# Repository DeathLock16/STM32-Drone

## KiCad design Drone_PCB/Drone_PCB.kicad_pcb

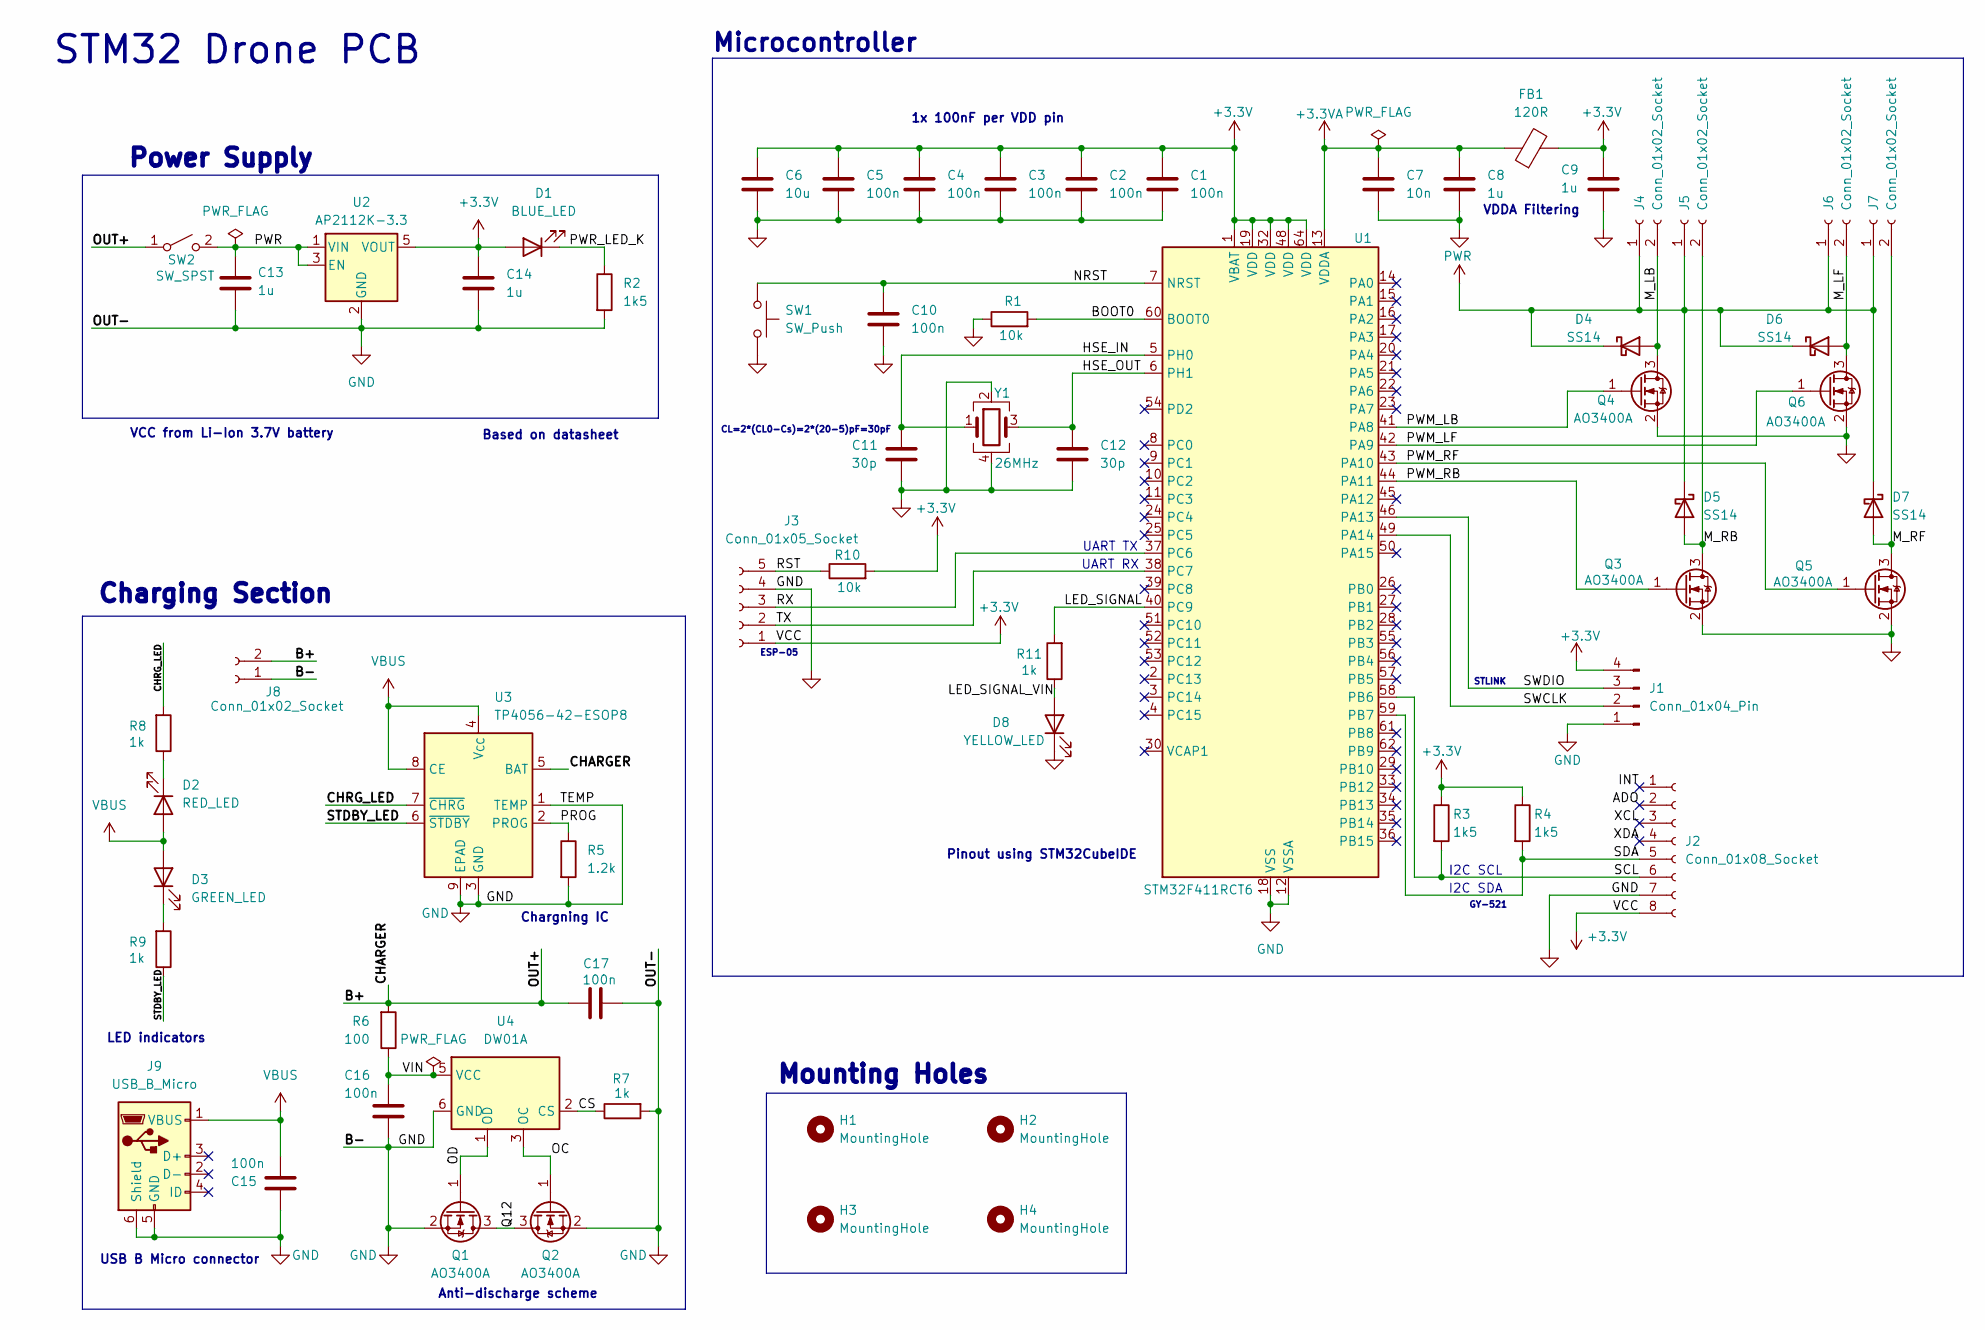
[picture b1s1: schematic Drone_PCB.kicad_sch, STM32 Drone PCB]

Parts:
C1, C2, C3, C4, C5, C10, C15, C16, C17: 100n; C_0402_1005Metric
C6: 10u; C_0603_1608Metric
C7: 10n; C_0402_1005Metric
C8, C9, C13, C14: 1u; C_0402_1005Metric
C11, C12: 30p; C_0402_1005Metric
D1: BLUE_LED; LED_0603_1608Metric
D2: RED_LED; LED_0603_1608Metric
D3: GREEN_LED; LED_0603_1608Metric
D4, D5, D6, D7: SS14; D_SMA
D8: YELLOW_LED; LED_0603_1608Metric
FB1: 120R; L_0603_1608Metric
H1, H2, H3, H4: MountingHole; MountingHole_2.2mm_M2
J1: Conn_01x04_Pin; PinHeader_1x04_P2.54mm_Vertical
J2: Conn_01x08_Socket; PinSocket_1x08_P2.54mm_Vertical
J3: Conn_01x05_Socket; PinSocket_1x05_P2.54mm_Vertical
J4, J5, J6, J7, J8: Conn_01x02_Socket; PinSocket_1x02_P2.54mm_Vertical
J9: USB_B_Micro; USB_Micro-B_Wuerth_629105150521
Q1, Q2, Q3, Q4, Q5, Q6: AO3400A; SOT-23
R1, R10: 10k; R_0402_1005Metric
R2, R3, R4: 1k5; R_0402_1005Metric
R5: 1.2k; R_0402_1005Metric
R6: 100; R_0402_1005Metric
R7, R8, R9, R11: 1k; R_0402_1005Metric
SW1: SW_Push; SW_PUSH_6mm
SW2: SW_SPST; SW_CK_JS202011AQN_DPDT_Angled
U1: STM32F411RCT6; LQFP-64_10x10mm_P0.5mm
U2: AP2112K-3.3; SOT-23-5
U3: TP4056-42-ESOP8; SOIC-8-1EP_3.9x4.9mm_P1.27mm_EP2.41x3.3mm_ThermalVias
U4: DW01A; SOT-23-6
Y1: 26MHz; Crystal_SMD_3225-4Pin_3.2x2.5mm

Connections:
+3.3V: C1.1, C2.1, C3.1, C4.1, C5.1, C6.1, C9.1, C14.1, D1.2 (A), FB1.2, J1.4, J2.8, J3.1, R3.1, R4.1, R10.2, U1.1 (VBAT), U1.19 (VDD), U1.32 (VDD), U1.48 (VDD), U1.64 (VDD), U2.5 (VOUT)
+3.3VA: C7.1, C8.1, FB1.1, U1.13 (VDDA)
/ADO: J2.2
/B+: C17.1, J8.2, R6.2, SW2.1 (A), U3.5 (BAT)
/BOOT0: R1.2, U1.60 (BOOT0)
/CHRG_LED: R8.2, U3.7 (~CHRG)
/CS: R7.1, U4.2 (CS)
/HSE_IN: C11.1, U1.5 (PH0), Y1.1
/HSE_OUT: C12.1, U1.6 (PH1), Y1.3
/INT: J2.1
/LED_SIGNAL: R11.2, U1.40 (PC9)
/LED_SIGNAL_VIN: D8.2 (A), R11.1
/M_LB: D4.2 (A), J4.2, Q4.3 (D)
/M_LF: D6.2 (A), J6.2, Q6.3 (D)
/M_RB: D5.2 (A), J5.2, Q3.3 (D)
/M_RF: D7.2 (A), J7.2, Q5.3 (D)
/NRST: C10.1, SW1.1, U1.7 (NRST)
/OC: Q2.1 (G), U4.3 (OC)
/OD: Q1.1 (G), U4.1 (OD)
/PROG: R5.1, U3.2 (PROG)
/PWM_LB: Q4.1 (G), U1.41 (PA8)
/PWM_LF: Q6.1 (G), U1.42 (PA9)
/PWM_RB: Q3.1 (G), U1.44 (PA11)
/PWM_RF: Q5.1 (G), U1.43 (PA10)
/PWR_LED_K: D1.1 (K), R2.1
/Q12: Q1.3 (D), Q2.3 (D)
/RST: J3.5, R10.1
/RX: J3.3, U1.37 (PC6)
/SCL: J2.6, R3.2, U1.58 (PB6)
/SDA: J2.5, R4.2, U1.59 (PB7)
/STDBY_LED: R9.1, U3.6 (~STDBY)
/SWCLK: J1.2, U1.49 (PA14)
/SWDIO: J1.3, U1.46 (PA13)
/TX: J3.2, U1.38 (PC7)
/VIN: C16.1, R6.1, U4.5 (VCC)
/XCL: J2.3
/XDA: J2.4
GND: C1.2, C2.2, C3.2, C4.2, C5.2, C6.2, C7.2, C8.2, C9.2, C10.2, C11.2, C12.2, C13.2, C14.2, C15.1, C16.2, C17.2, D8.1 (K), J1.1, J2.7, J3.4, J8.1, J9.5 (GND), J9.6 (Shield), Q1.2 (S), Q2.2 (S), Q3.2 (S), Q4.2 (S), Q5.2 (S), Q6.2 (S), R1.1, R2.2, R5.2, R7.2, SW1.2, U1.12 (VSSA), U1.18 (VSS), U1.31 (VSS), U1.47 (VSS), U1.63 (VSS), U2.2 (GND), U3.1 (TEMP), U3.3 (GND), U3.9 (EPAD), U4.6 (GND), Y1.2, Y1.4
unnamed: D2.1 (K), R8.1
unnamed: D3.1 (K), R9.2
PWR: C13.1, D4.1 (K), D5.1 (K), D6.1 (K), D7.1 (K), J4.1, J5.1, J6.1, J7.1, SW2.2 (B), U2.1 (VIN), U2.3 (EN)
VBUS: C15.2, D2.2 (A), D3.2 (A), J9.1 (VBUS), U3.4 (V_{CC}), U3.8 (CE)

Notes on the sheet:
CL=2*(CL0-Cs)=2*(20-5)pF=30pF
Mounting Holes
GY-521
Pinout using STM32CubeIDE
UART TX
USB B Micro connector
UART RX
Power Supply
LED indicators
Chargning IC
VCC from Li-Ion 3.7V battery
I2C SDA
STM32 Drone PCB
1x 100nF per VDD pin
Based on datasheet
ESP-05
Anti-discharge scheme
Microcontroller
Charging Section
VDDA Filtering
STLINK
I2C SCL

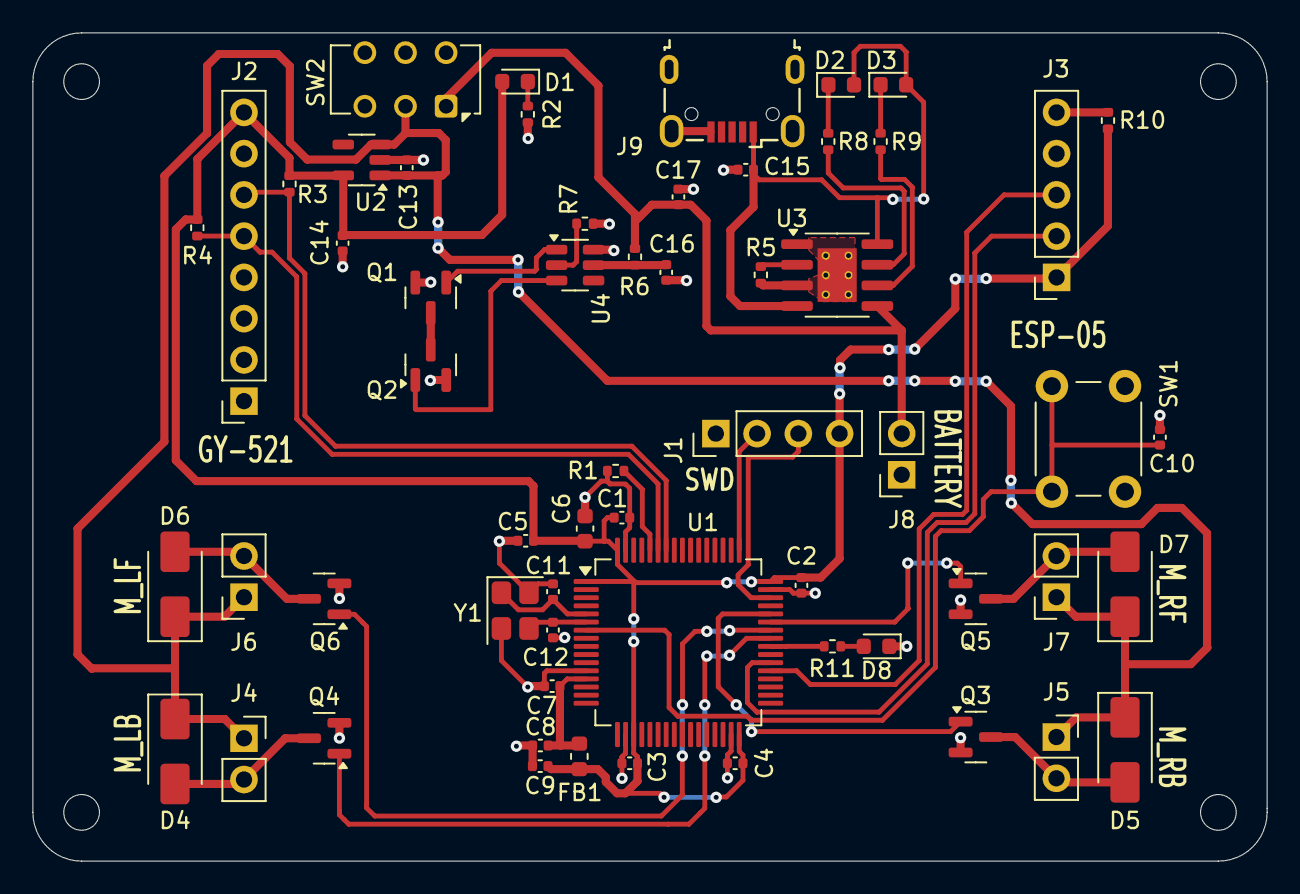
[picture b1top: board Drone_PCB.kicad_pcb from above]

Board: 2 copper layers, 76.0 x 51.0 mm, 63 parts (0 on the bottom side), 38 nets.

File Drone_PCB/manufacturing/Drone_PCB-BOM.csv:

"Reference","Qty","Value","DNP","Exclude from BOM","Exclude from Board","Footprint","Datasheet"
"C1,C2,C3,C4,C5,C10,C15,C16,C17","9","100n","","","","Capacitor_SMD:C_0402_1005Metric","~"
"C6","1","10u","","","","Capacitor_SMD:C_0603_1608Metric","~"
"C7","1","10n","","","","Capacitor_SMD:C_0402_1005Metric","~"
"C8,C9,C13,C14","4","1u","","","","Capacitor_SMD:C_0402_1005Metric","~"
"C11,C12","2","30p","","","","Capacitor_SMD:C_0402_1005Metric","~"
"D1","1","BLUE_LED","","","","LED_SMD:LED_0603_1608Metric","~"
"D2","1","RED_LED","","","","LED_SMD:LED_0603_1608Metric","~"
"D3","1","GREEN_LED","","","","LED_SMD:LED_0603_1608Metric","~"
"D4,D5,D6,D7","4","SS14","","","","Diode_SMD:D_SMA","https://www.vishay.com/docs/88746/ss12.pdf"
"D8","1","YELLOW_LED","","","","LED_SMD:LED_0603_1608Metric","~"
"FB1","1","120R","","","","Inductor_SMD:L_0603_1608Metric","~"
"J1","1","Conn_01x04_Pin","","","","Connector_PinHeader_2.54mm:PinHeader_1x04_P2.54mm_Vertical","~"
"J2","1","Conn_01x08_Socket","","","","Connector_PinSocket_2.54mm:PinSocket_1x08_P2.54mm_Vertical","~"
"J3","1","Conn_01x05_Socket","","","","Connector_PinSocket_2.54mm:PinSocket_1x05_P2.54mm_Vertical","~"
"J4,J5,J6,J7,J8","5","Conn_01x02_Socket","","","","Connector_PinSocket_2.54mm:PinSocket_1x02_P2.54mm_Vertical","~"
"J9","1","USB_B_Micro","","","","Connector_USB:USB_Micro-B_Wuerth_629105150521","~"
"Q1,Q2,Q3,Q4,Q5,Q6","6","AO3400A","","","","Package_TO_SOT_SMD:SOT-23","http://www.aosmd.com/pdfs/datasheet/AO3400A.pdf"
"R1,R10","2","10k","","","","Resistor_SMD:R_0402_1005Metric","~"
"R2,R3,R4","3","1k5","","","","Resistor_SMD:R_0402_1005Metric","~"
"R5","1","1.2k","","","","Resistor_SMD:R_0402_1005Metric","~"
"R6","1","100","","","","Resistor_SMD:R_0402_1005Metric","~"
"R7,R8,R9,R11","4","1k","","","","Resistor_SMD:R_0402_1005Metric","~"
"SW1","1","SW_Push","","","","Button_Switch_THT:SW_PUSH_6mm","~"
"SW2","1","SW_SPST","","","","Button_Switch_THT:SW_CK_JS202011AQN_DPDT_Angled","~"
"U1","1","STM32F411RCT6","","","","Package_QFP:LQFP-64_10x10mm_P0.5mm","https://www.st.com/resource/en/datasheet/stm32f411rc.pdf"
"U2","1","AP2112K-3.3","","","","Package_TO_SOT_SMD:SOT-23-5","https://www.diodes.com/assets/Datasheets/AP2112.pdf"
"U3","1","TP4056-42-ESOP8","","","","Package_SO:SOIC-8-1EP_3.9x4.9mm_P1.27mm_EP2.41x3.3mm_ThermalVias","https://www.lcsc.com/datasheet/lcsc_datasheet_2410121619_TOP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"
"U4","1","DW01A","","","","Package_TO_SOT_SMD:SOT-23-6","https://hmsemi.com/downfile/DW01A.PDF"
"Y1","1","26MHz","","","","Crystal:Crystal_SMD_3225-4Pin_3.2x2.5mm","~"

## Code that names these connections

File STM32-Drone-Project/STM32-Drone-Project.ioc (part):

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Mcu.Name=STM32F411R(C-E)Tx
Mcu.Package=LQFP64
Mcu.UserName=STM32F411RCTx
PA10.GPIOParameters=GPIO_Label
PA10.GPIO_Label=MOTOR_RF
PA10.Signal=S_TIM1_CH3
PA11.GPIOParameters=GPIO_Label
PA11.GPIO_Label=MOTOR_RB
PA11.Signal=S_TIM1_CH4
PA13.Mode=Serial_Wire
PA13.Signal=SYS_JTMS-SWDIO
PA14.Mode=Serial_Wire
PA14.Signal=SYS_JTCK-SWCLK
PA8.GPIOParameters=GPIO_Label
PA8.GPIO_Label=MOTOR_LB
PA8.Signal=S_TIM1_CH1
PA9.GPIOParameters=GPIO_Label
PA9.GPIO_Label=MOTOR_LF
PA9.Signal=S_TIM1_CH2
PB6.Mode=I2C
PB6.Signal=I2C1_SCL
PB7.Mode=I2C
PB7.Signal=I2C1_SDA
PC14-OSC32_IN.Mode=LSE-External-Oscillator
PC14-OSC32_IN.Signal=RCC_OSC32_IN
PC15-OSC32_OUT.Mode=LSE-External-Oscillator
PC15-OSC32_OUT.Signal=RCC_OSC32_OUT
PC6.Mode=Asynchronous
PC6.Signal=USART6_TX
PC7.Mode=Asynchronous
PC7.Signal=USART6_RX
PC9.GPIOParameters=GPIO_Label
PC9.GPIO_Label=LED_SIGNAL
PC9.Signal=GPIO_Output
PH0\ -\ OSC_IN.Mode=HSE-External-Oscillator
PH0\ -\ OSC_IN.Signal=RCC_OSC_IN
PH1\ -\ OSC_OUT.Mode=HSE-External-Oscillator
PH1\ -\ OSC_OUT.Signal=RCC_OSC_OUT
RCC.HSE_VALUE=26000000
RCC.SYSCLKFreq_VALUE=26000000
RCC.SYSCLKSource=RCC_SYSCLKSOURCE_HSE
board=custom

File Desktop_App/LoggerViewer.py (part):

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
        self.ax_pwm.set_title("PWM")
        self.ax_pwm.set_ylabel("pwm")
        self.ax_pwm.plot(t, df["pwm_lf"].values, label="pwm_lf")
        self.ax_pwm.plot(t, df["pwm_rf"].values, label="pwm_rf")
        self.ax_pwm.plot(t, df["pwm_lb"].values, label="pwm_lb")
        self.ax_pwm.plot(t, df["pwm_rb"].values, label="pwm_rb")
        self.ax_pwm.grid(True, alpha=0.25)
        self.ax_pwm.legend(loc="upper right")

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
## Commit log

2025-06-19 Created KiCad project
    We'll create PCB Board by ourselves
2025-06-19 Created STM32 CubeIDE Project
    Our chosen MCU: STM32F411RCT6
2025-06-19 First scheme
    Added MCU + VSS/VDD
2025-06-21 Power output
    NRST and BOOT0 pins are now connected.
    NRST via Capacitor to GND
    BOOT0 via 10k Resistor to GND ( enable SWD programming )
2025-06-21 Outputs
    Created outputs in our STM32 CubeIDE Project and in KiCad:
    - SWD
    - RCC_OSC
    - USART1
    - I2C1
    - MOTORs
2025-06-21 Crystal Oscillator
    I've decided to pick this one:
    https://www.tme.eu/pl/details/26.00m-smdhc49s/rezonatory-kwarcowe-smd/yic/
    It has 26MHz ( it's maximum input from STM Cube IDE ). It has 20pF, so to calculate two other capacitors we do this: 20pF - 5pF (that's maximum constant value)
    15pF * 2 = 30pF each
2025-06-22 Voltage regulator + Outputs
    I selected AP2112K as voltage regulator from 5/3.7V to 3.3V.
    https://www.tme.eu/pl/details/ap2112k-3.3trg1/stabilizatory-napiecia-nieregulowane-ldo/diodes-incorporated/
    In future I will add charging module
2025-06-22 Notes and other output
    Added outputs for LED_SIGNAL, MOTORs and proper connection of SWD. Also added schmatic notes
2025-06-22 Added charging module
    FIX THAT connections are wrong 4some reason
2025-06-23 Fixed errors
    Now everything looks good
2025-06-23 Footprint assignment
    We assigned footprints
2025-06-23 Updated footprint
    There were missing objects
2025-06-23 Creating PCB part 1
    Circuit is looking pretty neat
2025-08-26 Adjusted some pinouts
    Corrected pinouts for motors leds and communication modules
2025-08-26 Updated motors
    We control MOSFETS with PWM so there will not be any overcurrent
2025-08-26 Updated charging section
    Changed NMOS transistors + diodes to VBUS
2025-11-04 Added NRST button
    Following the advice of Dr. Puchalski, I added NRST button. Additionally, I tidied up the engine area more.
2025-11-04 Switching THD Signal LED to SMD
    It will be better I guess
2025-11-04 Changed TP4056 symbol
    BAT is passive now due to KiCad errors about multiple Power Outputs
2025-11-04 Battery output + changing few things
    Absolutely forgot about power source socket ( battery )
2025-11-04 Chose elements
    I guess it's all of them
2025-11-04 PCB #1
    MCU, Decoupling Capacitors and Crystal layout
2025-11-04 SWD Layout
    Added SWD pinout
2025-11-04 Fixed missing models
    Sike
2025-11-04 Arranged I2C, UART and SWD
    It looks okay
2025-11-04 PCB #2
    Created charging section
2025-11-04 PCB #3
    Added motors
2025-11-04 PCB #4
    Connected signal LED, everything is connected
2025-11-05 Fast update
    PCB didn't save last time
2025-11-09 Added Mounting Holers + Edges
    Now PCB is almost ready in 3D terms
2025-11-28 Created router using FreeRouting
    We switched Bottom Layer to signal to enable FreeRouting
2025-11-28 Increase drill size and add silkscreen labels
    Updated several pad drill sizes from 0.2mm to 0.3mm for improved manufacturability. Added silkscreen text labels for connectors and components, and updated PCB routing and backup files to reflect lat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
2025-11-28 Update PCB backup file
    Replaced the previous PCB backup (2025-11-28_123159.zip) with a new version (2025-11-28_145056.zip) to maintain up-to-date project backups.
2025-11-28 Update PCB project and add manufacturing files
    Updated PCB and project files to output manufacturing data to the 'manufacturing/' directory. Added Gerber, drill, BOM, position, and STL files for fabrication. Removed obsolete backup and lock files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
2025-12-04 Changed schematic
    FreeRouting does kinda lame job. Removed routes and moved some elements
2025-12-04 Added GND routes
    It should work okay now
2025-12-04 Made the rest of routes-ish
    Sort of
2025-12-05 Full routing
    Man, that was hard
2025-12-05 Final routes
    I guess it's okay now
2025-12-16 Last touches
    All changes exported to JLCPCB
2025-12-28 STM32 Gyroscope code
    Used Madgwick to read data and Blender script for simulating Drone movement
2025-12-28 Switched already to ESP-05 communication
    4some reason I have to click Reset button on start, my fault I guess during the scheme creation. Anyway, communication is via WiFi
2025-12-29 Frames system
    From now on, we can calculate frames and send/receive them
2025-12-29 Switched to 10k PWM
    That value seems more logical to set. Made new commands in test script. Note - motor drains too much current, we have to add Capacitor.
2025-12-30 Added IMU Frame
    We're recalculating it in while loop, so data will always be somehow proper
2026-01-22 Created 3D models
2026-01-23 Used OrcaSlicer for slicing 3d model
2026-01-24 Added acceleration filter + shut-off
    If the angle is >= 45 degrees, then PWMs are shut off
2026-01-24 Auto stabilization
    + KP regulator
2026-01-24 Updated failed start
    Also fixed a bug
2026-01-24 Added armed flag
2026-01-24 Added YAW balance
    It will not rotate as much as before
2026-01-24 Created control app
    For controlling drone
2026-01-24 Fixed small bug
    Repetition of variable
2026-01-25 Added best possible filtration
    For now, the weight (79g) is just too big, so the basic movement is possible only
2026-01-25 Created 3d model viewer
    We will update it soon
2026-01-25 Updated 3D viewer
2026-01-25 Resigned from 3D viewer
    Was not working well
2026-01-25 Updated model
    Not it's current model
2026-01-25 PID tuning
2026-01-25 Added AUTO RAMP
    It increases smoothly the PWM
2026-01-25 Added PWM plots
    It helps diagnosing errors
2026-01-25 Created telemetry frame
    It sends all telemetry data in 1 packet
2026-01-26 Tuning again
2026-01-26 Created ground testing environment
    Turns will be more aggresive
2026-01-27 Desktop app exports data
    It exports telemetry data for tuning. Also added navigation directions
2026-01-28 Tuning again
    Created new model with support from below for imu stabilization
2026-01-29 Tuning
2026-02-01 Last tuning
2026-02-05 IMU calibration
    Changed a way that IMU calibrates itself and added new telemetry frame
2026-02-10 Final tuning + Logger app + a lot
    Changed kinda lot
2026-02-18 Include thesis
2026-02-23 Final fixes
2026-03-01 Updated blender file
    Simulation now shows only IMU, Telemetry is useless for this
